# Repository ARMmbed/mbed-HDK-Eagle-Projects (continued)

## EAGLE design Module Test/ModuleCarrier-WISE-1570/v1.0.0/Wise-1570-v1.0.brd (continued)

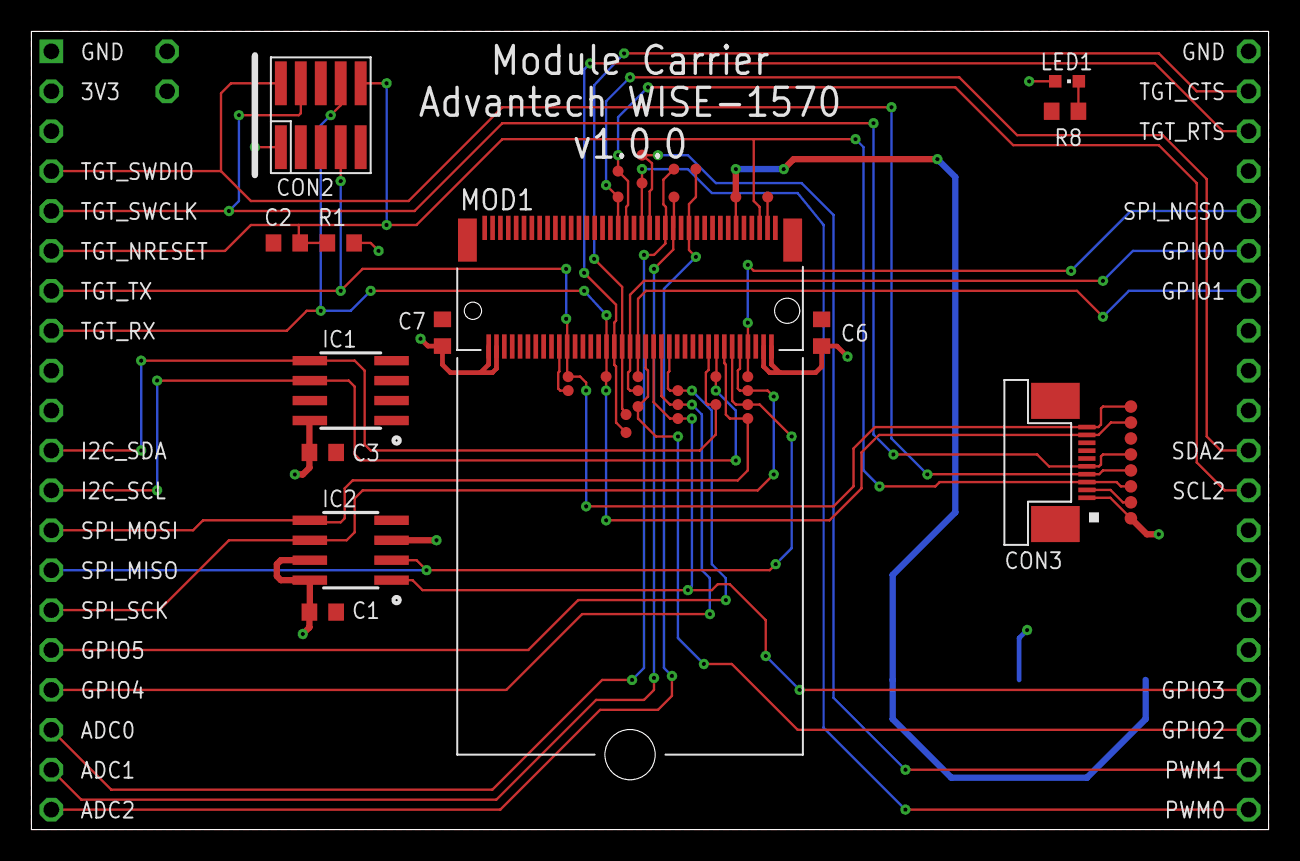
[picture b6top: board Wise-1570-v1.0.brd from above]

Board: 2 copper layers, 78.7 x 50.8 mm, 52 parts (1 on the bottom side), 33 nets.

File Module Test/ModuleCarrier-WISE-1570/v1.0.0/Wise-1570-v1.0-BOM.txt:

Partlist exported from C:/Users/cstyles/OneDrive - Arm/Documents/mbed/Projects/blackbriar/ModuleCarrier-WISE-1570/v1.0.0/Wise-1570-v1.0.sch at 15/01/2018 11:27

Qty Value              Device             Package         Parts                                                                                                                                                     Description                                                                                          
5   100nF              CAPACITOR0603      0603            C1, C2, C3, C6, C7                                                                                                                                        Capacitor                                                                                            
1   10k                RESISTOR0603       0603            R1                                                                                                                                                        Resistor                                                                                             
1   1k                 RESISTOR0603       0603            R8                                                                                                                                                        Resistor                                                                                             
1   3030               3030               3030            BAT1                                                                                                                                                      CR927, CR1025 Battery Holder for 9-10mm Cells-Tin Nickel Plated SMD                                  
1   ATECC608A          ATECC608A          SO8             IC1                                                                                                                                                                                                                                                            
1   FLOSSICORN0.25     FLOSSICORN0.25     FLOSSICORN-0.25 SS1                                                                                                                                                                                                                                                            
1   MODULE_DAUGHTER    MODULE_DAUGHTER    MODULE_DAUGHTER MOD2                                                                                                                                                                                                                                                           
1   MX25R3235FM1IH0    MX25R3235FM1IH0    SO8             IC2                                                                                                                                                       Serial Flash 32 Mb 80 Mhz                                                                            
26  PTR1TP07R          PTR1TP07R          TP07R           TP9, TP10, TP11, TP14, TP15, TP16, TP17, TP18, TP19, TP20, TP21, TP22, TP23, TP24, TP25, TP26, TP27, TP28, TP29, TP30, TP31, TP32, TP33, TP34, TP35, TP36 TEST PIN                                                                                             
8   PTR1TP08R          PTR1TP08R          TP08R           TP3, TP4, TP5, TP6, TP7, TP8, TP12, TP13                                                                                                                  TEST PIN                                                                                             
1   RED                SMD_LED0603        CHIPLED_0603    LED1                                                                                                                                                      LED SMD, Colour Red                                                                                  
1   SWD-10/TC2050_SMD  SWD-10/TC2050_SMD  FTSH-105-02     CON2                                                                                                                                                      1mm pitch 10-Pin Cortex Programming Header with optional TC2050 footprint solderless interchangeable 
1   TE-1-1734592-0     TE-1-1734592-0     TE-1-1734592-0  CON3                                                                                                                                                                                                                                                           
2   TEST-POINT-50R-PTH TEST-POINT-50R-PTH TP50-PTH        TP1, TP2                                                                                                                                                                                                                                                       
1   WISE-1570          WISE-1570          MDT420E02001    MOD1

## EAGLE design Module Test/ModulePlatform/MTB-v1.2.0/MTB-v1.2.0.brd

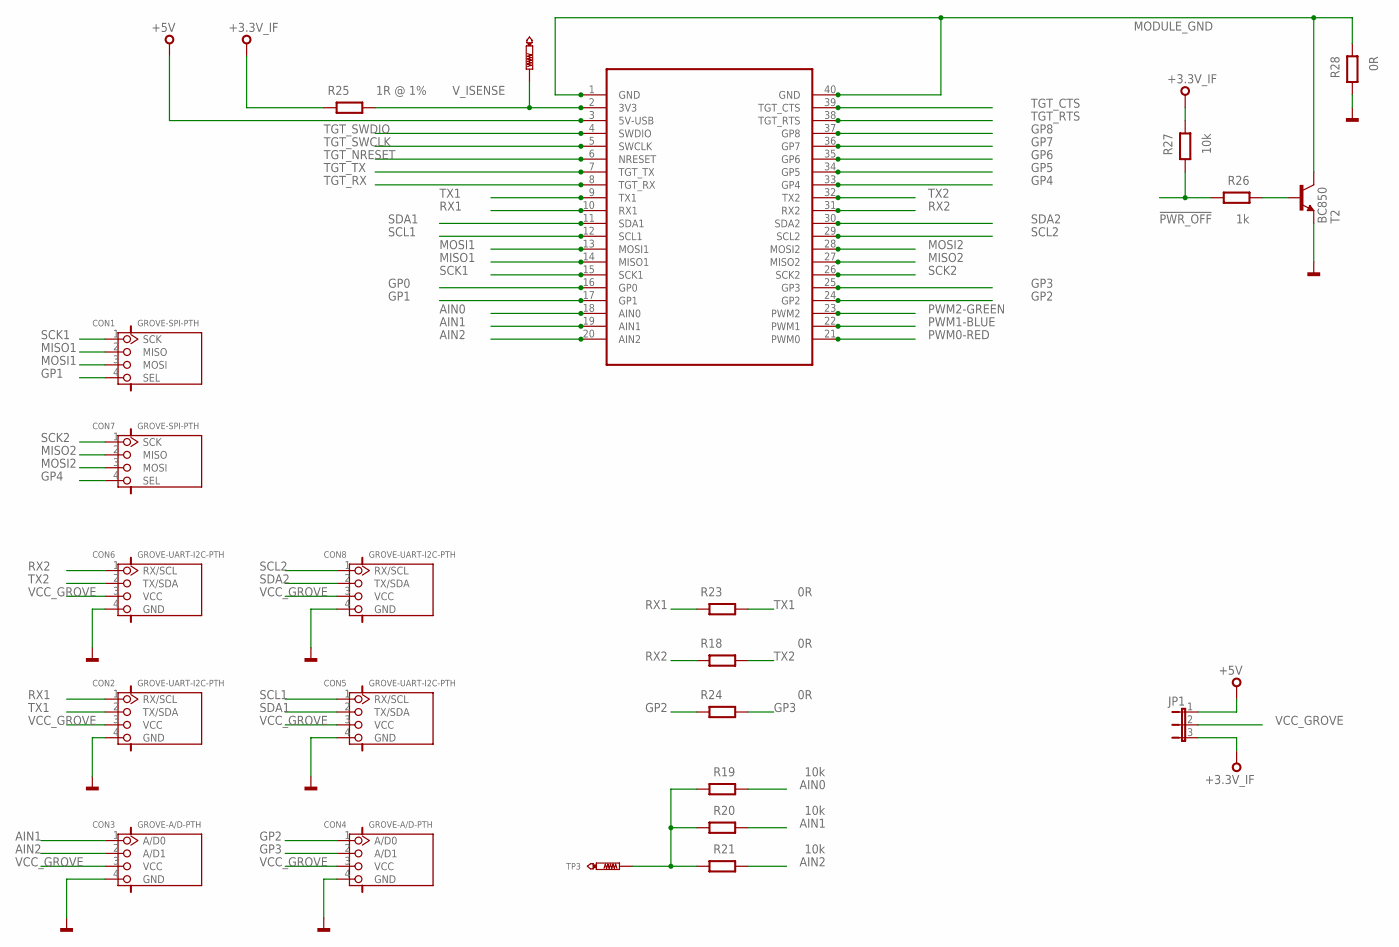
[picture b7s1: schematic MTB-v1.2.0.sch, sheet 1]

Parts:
CON1, CON7: GROVE-SPI-PTH; HW4-2.0
CON2, CON5, CON6, CON8: GROVE-UART-I2C-PTH; HW4-2.0
CON3, CON4: GROVE-A/D-PTH; HW4-2.0
JP1: JP2E; JP2
R18, R23, R24, R28: 0R; 0603@1
R19, R20, R21, R27: 10k; 0603@1
R25: 1R @ 1%; 0603@1
R26: 1k; 0603@1
SKT1: MODULE_SOCKET
T2: BC850; SOT23
TP3: TEST-POINT-50R-PTH; TP50-PTH
TP8: PTR1TP07R; TP07R

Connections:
!PWR_OFF: R26.2, R27.2; also elsewhere on the board
+3.3V_IF: JP1.3, R25.2, R27.1; also elsewhere on the board
+5V: JP1.1, SKT1.3 (5V-USB), SKT1.P$43; also elsewhere on the board
AIN0: R19.1, SKT1.18 (AIN0), SKT1.P$58; also elsewhere on the board
AIN1: CON3.1 (A/D0), R20.1, SKT1.19 (AIN1), SKT1.P$59
AIN2: CON3.2 (A/D1), R21.1, SKT1.20 (AIN2), SKT1.P$60
GND: CON2.4 (GND), CON3.4 (GND), CON4.4 (GND), CON5.4 (GND), CON6.4 (GND), CON8.4 (GND), R28.2, T2.2 (E); also elsewhere on the board
GP0: SKT1.16 (GP0), SKT1.P$56; also elsewhere on the board
GP1: CON1.4 (SEL), SKT1.17 (GP1), SKT1.P$57
GP2: CON4.1 (A/D0), R24.2, SKT1.24 (GP2), SKT1.P$64; also elsewhere on the board
GP3: CON4.2 (A/D1), R24.1, SKT1.25 (GP3), SKT1.P$65
GP4: CON7.4 (SEL), SKT1.33 (GP4), SKT1.P$73
GP5: SKT1.34 (GP5), SKT1.P$74; also elsewhere on the board
GP6: SKT1.35 (GP6), SKT1.P$75; also elsewhere on the board
GP7: SKT1.36 (GP7), SKT1.P$76; also elsewhere on the board
GP8: SKT1.37 (GP8), SKT1.P$77
MISO1: CON1.2 (MISO), SKT1.14 (MISO1), SKT1.P$54; also elsewhere on the board
MISO2: CON7.2 (MISO), SKT1.27 (MISO2), SKT1.P$67
MODULE_GND: R28.1, SKT1.1 (GND), SKT1.40 (GND), SKT1.P$41, SKT1.P$80, T2.3 (C)
MOSI1: CON1.3 (MOSI), SKT1.13 (MOSI1), SKT1.P$53; also elsewhere on the board
MOSI2: CON7.3 (MOSI), SKT1.28 (MOSI2), SKT1.P$68
unnamed: R19.2, R20.2, R21.2, TP3.TP
unnamed: R26.1, T2.1 (B)
PWM0-RED: SKT1.21 (PWM0), SKT1.P$61; also elsewhere on the board
PWM1-BLUE: SKT1.22 (PWM1), SKT1.P$62; also elsewhere on the board
PWM2-GREEN: SKT1.23 (PWM2), SKT1.P$63; also elsewhere on the board
RX1: CON2.1 (RX/SCL), R23.2, SKT1.10 (RX1), SKT1.P$50
RX2: CON6.1 (RX/SCL), R18.2, SKT1.31 (RX2), SKT1.P$71
SCK1: CON1.1 (SCK), SKT1.15 (SCK1), SKT1.P$55; also elsewhere on the board
SCK2: CON7.1 (SCK), SKT1.26 (SCK2), SKT1.P$66
SCL1: CON5.1 (RX/SCL), SKT1.12 (SCL1), SKT1.P$52; also elsewhere on the board
SCL2: CON8.1 (RX/SCL), SKT1.29 (SCL2), SKT1.P$69; also elsewhere on the board
SDA1: CON5.2 (TX/SDA), SKT1.11 (SDA1), SKT1.P$51; also elsewhere on the board
SDA2: CON8.2 (TX/SDA), SKT1.30 (SDA2), SKT1.P$70; also elsewhere on the board
TGT_CTS: SKT1.39 (TGT_CTS), SKT1.P$79; also elsewhere on the board
TGT_NRESET: SKT1.6 (NRESET), SKT1.P$46; also elsewhere on the board
TGT_RTS: SKT1.38 (TGT_RTS), SKT1.P$78; also elsewhere on the board
TGT_RX: SKT1.8 (TGT_RX), SKT1.P$48; also elsewhere on the board
TGT_SWCLK: SKT1.5 (SWCLK), SKT1.P$45; also elsewhere on the board
TGT_SWDIO: SKT1.4 (SWDIO), SKT1.P$44; also elsewhere on the board
TGT_TX: SKT1.7 (TGT_TX), SKT1.P$47; also elsewhere on the board
TX1: CON2.2 (TX/SDA), R23.1, SKT1.9 (TX1), SKT1.P$49
TX2: CON6.2 (TX/SDA), R18.1, SKT1.32 (TX2), SKT1.P$72
VCC_GROVE: CON2.3 (VCC), CON3.3 (VCC), CON4.3 (VCC), CON5.3 (VCC), CON6.3 (VCC), CON8.3 (VCC), JP1.2
V_ISENSE: R25.1, SKT1.2 (3V3), SKT1.P$42, TP8.TP; also elsewhere on the board

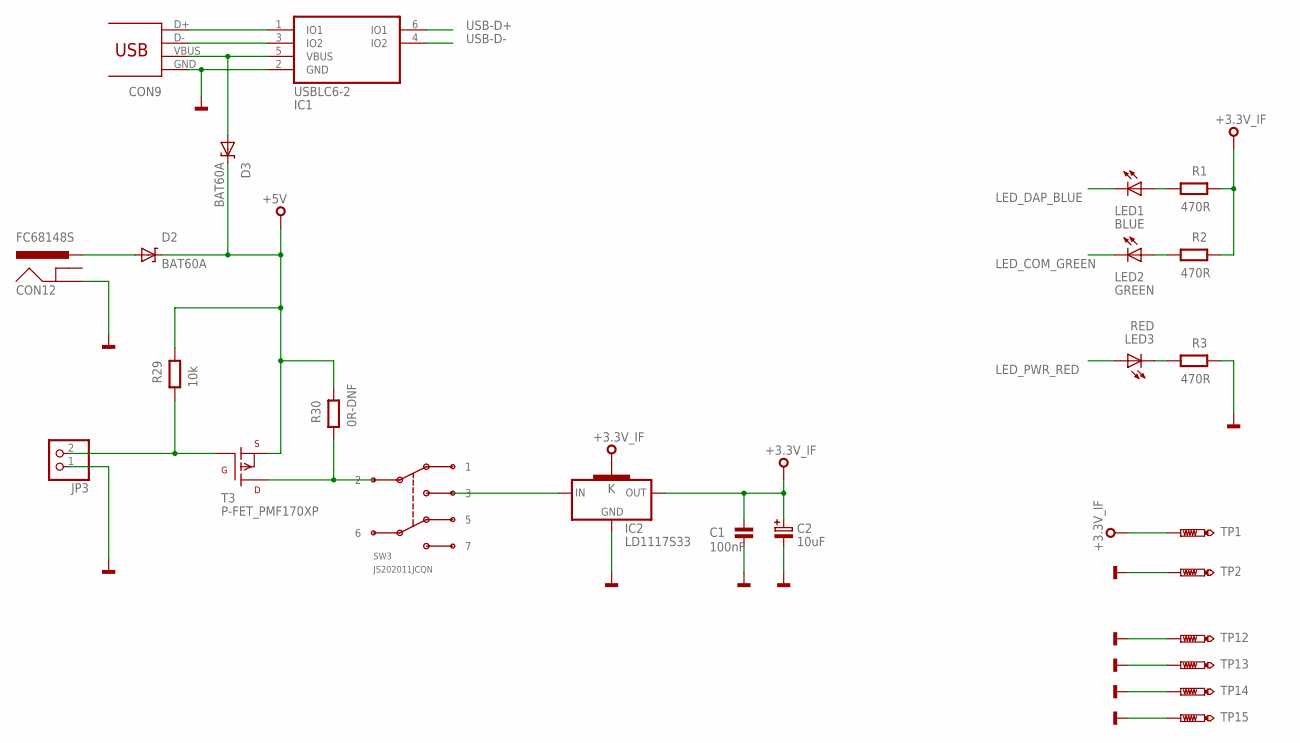
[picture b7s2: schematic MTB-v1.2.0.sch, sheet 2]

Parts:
C1: 100nF; 0603
C2: 10uF; SMC_B
CON9: USB_MICROB; MOLEX-47364-0001
CON12: FC68148S
D2, D3: BAT60A; SOD323
IC1: USBLC6-2SC6; SOT23-6L
IC2: LD1117S33; SOT223
JP3: PINHD-1X2; 1X02
LED1: BLUE; CHIPLED_0603
LED2: GREEN; CHIPLED_0603
LED3: RED; CHIPLED_0603
R1, R2, R3: 470R; 0603@1
R29: 10k; 0603@1
R30: 0R-DNF; 0603@1
SW3: JS202011JCQN
T3: P-FET_PMF170XP; SOT23-BEC
TP1, TP2, TP12, TP13, TP14, TP15: TEST-POINT-50R-PTH; TP50-PTH

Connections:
+3.3V_IF: C1.1, C2.+, IC2.2 (OUT), IC2.4 (K), R1.1, R2.1, TP1.TP; also elsewhere on the board
+5V: D2.K, D3.K, R29.1, R30.1, T3.E (S); also elsewhere on the board
GND: C1.2, C2.-, CON9.GND, CON12.3 (GND), IC1.2 (GND), IC2.1 (GND), JP3.1, R3.1, TP2.TP, TP12.TP, TP13.TP, TP14.TP, TP15.TP; also elsewhere on the board
LED_COM_GREEN: LED2.C; also elsewhere on the board
LED_DAP_BLUE: LED1.C; also elsewhere on the board
LED_PWR_RED: LED3.A; also elsewhere on the board
unnamed: CON9.D+, IC1.1 (IO1)
unnamed: CON9.D-, IC1.3 (IO2)
unnamed: LED2.A, R2.2
unnamed: LED3.C, R3.2
unnamed: LED1.A, R1.2
unnamed: CON9.VBUS, D3.A, IC1.5 (VBUS)
unnamed: R30.2, SW3.2, T3.C (D)
unnamed: CON12.1-1 (PWR), CON12.1-2 (PWR), D2.A
unnamed: IC2.3 (IN), SW3.3
unnamed: JP3.2, R29.2, T3.B (G)
USB-D+: IC1.6 (IO1); also elsewhere on the board
USB-D-: IC1.4 (IO2); also elsewhere on the board

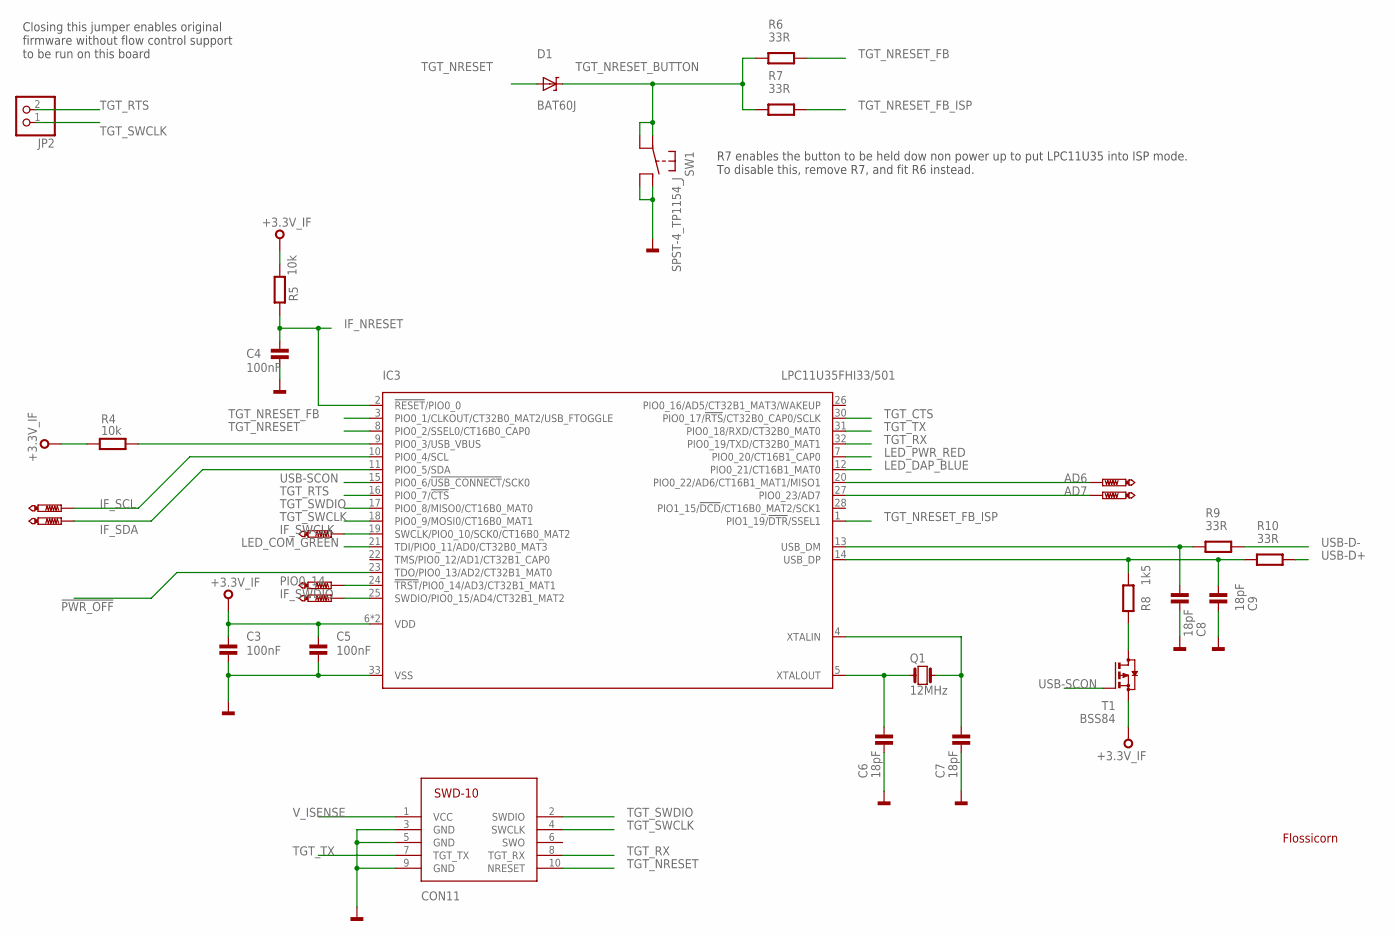
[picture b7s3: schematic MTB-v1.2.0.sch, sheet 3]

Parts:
C3, C4, C5: 100nF; 0603
C6, C7, C8, C9: 18pF; 0603
CON11: SWD-10/TC2050_SMD; FTSH-105-02
D1: BAT60J; BAT60A
IC3: LPC11U35FHI33/501; SOT617-3
JP2: PINHD-1X2; 1X02
Q1: 12MHz; 3.2X.2.5
R4, R5: 10k; 0603@1
R6, R7, R9, R10: 33R; 0603@1
R8: 1k5; 0603@1
SS1: FLOSSICORN0.5; FLOSSICORN-0.5
SW1: SPST-4_TP1154_J; TP-1154X
T1: BSS84; SOT23
TP4, TP5, TP6, TP7, TP9, TP10, TP11: PTR1TP07R; TP07R

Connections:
!PWR_OFF: IC3.23 (TDO/PIO0_13/AD2/CT32B1_MAT0); also elsewhere on the board
+3.3V_IF: C3.1, C5.1, IC3.6 (VDD), IC3.29 (VDD), R4.2, R5.2, T1.2 (S); also elsewhere on the board
AD6: IC3.20 (PIO0_22/AD6/CT16B1_MAT1/MISO1), TP7.TP
AD7: IC3.27 (PIO0_23/AD7), TP6.TP
GND: C3.2, C4.2, C5.2, C6.2, C7.2, C8.2, C9.2, CON11.3 (GND), CON11.5 (GND), CON11.9 (GND), IC3.33 (VSS), SW1.B1, SW1.B2; also elsewhere on the board
IF_NRESET: C4.1, IC3.2 (!RESET!/PIO0_0), R5.1
IF_SCL: IC3.10 (PIO0_4/SCL), TP4.TP
IF_SDA: IC3.11 (PIO0_5/SDA), TP5.TP
IF_SWCLK: IC3.19 (SWCLK/PIO0_10/SCK0/CT16B0_MAT2), TP10.TP
IF_SWDIO: IC3.25 (SWDIO/PIO0_15/AD4/CT32B1_MAT2), TP9.TP
LED_COM_GREEN: IC3.21 (TDI/PIO0_11/AD0/CT32B0_MAT3); also elsewhere on the board
LED_DAP_BLUE: IC3.12 (PIO0_21/CT16B1_MAT0); also elsewhere on the board
LED_PWR_RED: IC3.7 (PIO0_20/CT16B1_CAP0); also elsewhere on the board
unnamed: IC3.9 (PIO0_3/USB_VBUS), R4.1
unnamed: C6.1, IC3.5 (XTALOUT), Q1.P$1 (1)
unnamed: C7.1, IC3.4 (XTALIN), Q1.P$3 (2)
unnamed: R8.1, T1.3 (D)
PIO0_14: IC3.24 (!TRST!/PIO0_14/AD3/CT32B1_MAT1), TP11.TP
TGT_CTS: IC3.30 (PIO0_17/!RTS!/CT32B0_CAP0/SCLK); also elsewhere on the board
TGT_NRESET: CON11.10 (NRESET), D1.A, IC3.8 (PIO0_2/SSEL0/CT16B0_CAP0); also elsewhere on the board
TGT_NRESET_BUTTON: D1.K, R6.2, R7.2, SW1.A1, SW1.A2
TGT_NRESET_FB: IC3.3 (PIO0_1/CLKOUT/CT32B0_MAT2/USB_FTOGGLE), R6.1
TGT_NRESET_FB_ISP: IC3.1 (PIO1_19/!DTR!/SSEL1), R7.1
TGT_RTS: IC3.16 (PIO0_7/!CTS!), JP2.2; also elsewhere on the board
TGT_RX: CON11.8 (TGT_RX), IC3.32 (PIO0_19/TXD/CT32B0_MAT1); also elsewhere on the board
TGT_SWCLK: CON11.4 (SWCLK), IC3.18 (PIO0_9/MOSI0/CT16B0_MAT1), JP2.1; also elsewhere on the board
TGT_SWDIO: CON11.2 (SWDIO), IC3.17 (PIO0_8/MISO0/CT16B0_MAT0); also elsewhere on the board
TGT_TX: CON11.7 (TGT_TX), IC3.31 (PIO0_18/RXD/CT32B0_MAT0); also elsewhere on the board
USB-D+: R10.1; also elsewhere on the board
USB-D-: R9.1; also elsewhere on the board
USB-SCON: IC3.15 (PIO0_6/!USB_CONNECT!/SCK0), T1.1 (G)
USB_DM: C8.1, IC3.13 (USB_DM), R9.2
USB_DP: C9.1, IC3.14 (USB_DP), R8.2, R10.2
V_ISENSE: CON11.1 (VCC); also elsewhere on the board

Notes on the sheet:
R7 enables the button to be held dow non power up to put LPC11U35 into ISP mode. To disable this, remove R7, and fit R6 instead.
Closing this jumper enables original firmware without flow control support to be run on this board

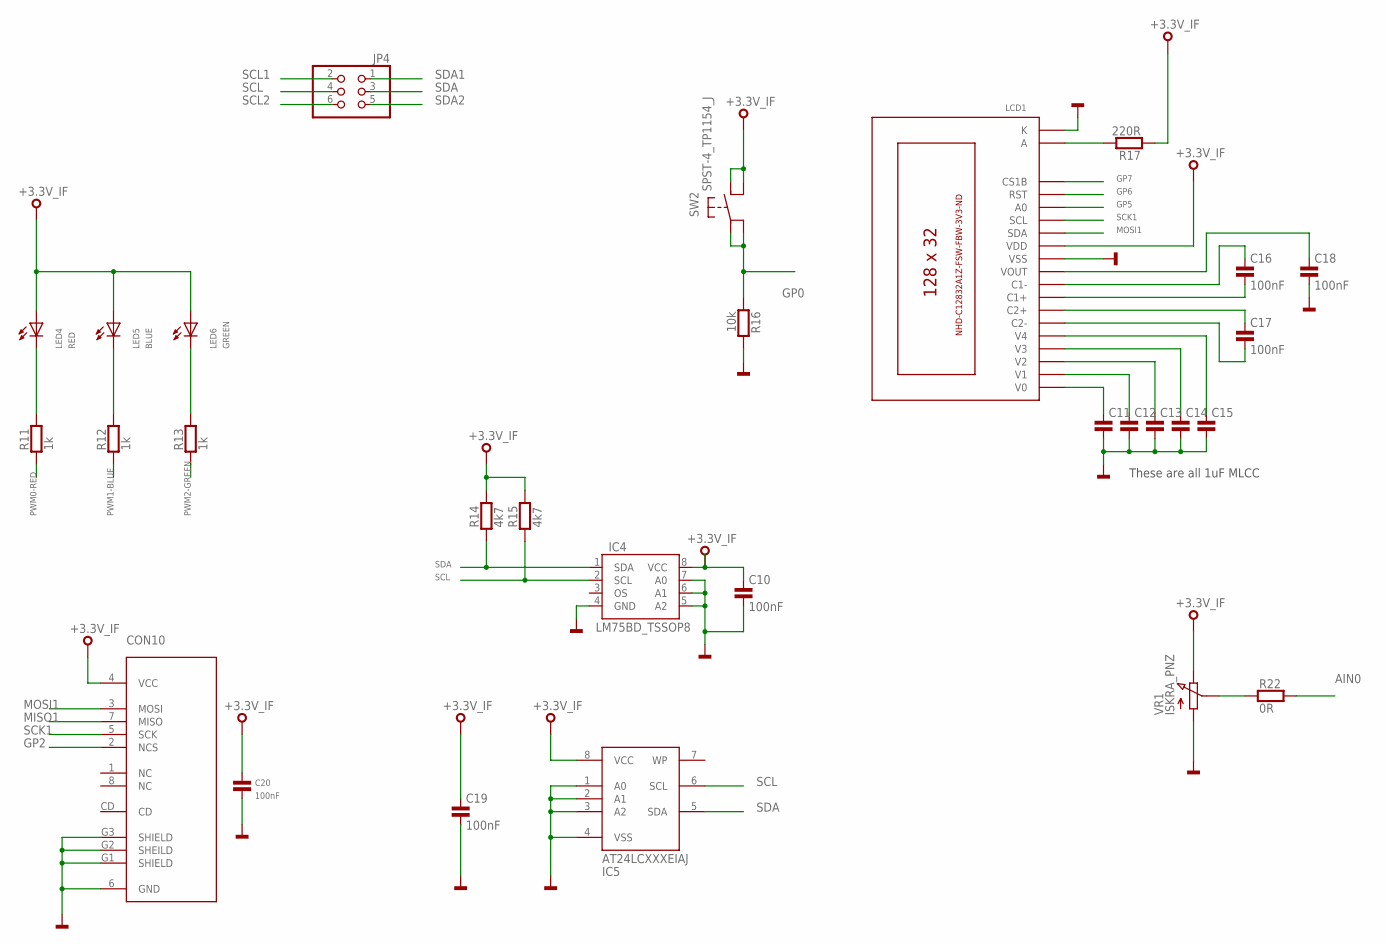
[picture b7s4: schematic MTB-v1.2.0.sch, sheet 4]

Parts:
C10, C11, C12, C13, C14, C15, C16, C17, C18, C19, C20: 100nF; 0603
CON10: MICRO-SD; AMPHENOL-101-00660-68-6
IC4: LM75BD_TSSOP8; TSSOP8
IC5: AT24LCXXXEIAJ; SO08-EIAJ
JP4: PINHD-2X3; 2X03
LCD1: C12832A1Z
LED4: RED; CHIPLED_0603
LED5: BLUE; CHIPLED_0603
LED6: GREEN; CHIPLED_0603
R11, R12, R13: 1k; 0603
R14, R15: 4k7; 0603
R16: 10k; 0603
R17: 220R; 0603
R22: 0R; 0603
SW2: SPST-4_TP1154_J; TP-1154X
VR1: ISKRA_PNZ; CA14V

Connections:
+3.3V_IF: C10.1, C19.1, C20.1, CON10.4 (VCC), IC4.8 (VCC), IC5.8 (VCC), LCD1.P$12 (VDD), LED4.A, LED5.A, LED6.A, R14.2, R15.2, R17.1, SW2.B1, SW2.B2, VR1.P$3 (E); also elsewhere on the board
AIN0: R22.2; also elsewhere on the board
GND: C10.2, C11.2, C12.2, C13.2, C14.2, C15.2, C18.2, C19.2, C20.2, CON10.6 (GND), CON10.G1 (SHIELD), CON10.G2 (SHEILD), CON10.G3 (SHIELD), IC4.4 (GND), IC4.5 (A2), IC4.6 (A1), IC4.7 (A0), IC5.1 (A0), IC5.2 (A1), IC5.3 (A2), IC5.4 (VSS), LCD1.K, LCD1.P$11 (VSS), R16.2, VR1.P$1 (A); also elsewhere on the board
GP0: R16.1, SW2.A1, SW2.A2; also elsewhere on the board
GP2: CON10.2 (NCS); also elsewhere on the board
GP5: LCD1.P$15 (A0); also elsewhere on the board
GP6: LCD1.P$16 (RST); also elsewhere on the board
GP7: LCD1.P$17 (CS1B); also elsewhere on the board
MISO1: CON10.7 (MISO); also elsewhere on the board
MOSI1: CON10.3 (MOSI), LCD1.P$13 (SDA); also elsewhere on the board
unnamed: C16.1, LCD1.P$9 (C1-)
unnamed: C17.1, LCD1.P$7 (C2+)
unnamed: C17.2, LCD1.P$6 (C2-)
unnamed: C16.2, LCD1.P$8 (C1+)
unnamed: C11.1, LCD1.P$1 (V0)
unnamed: C12.1, LCD1.P$2 (V1)
unnamed: C13.1, LCD1.P$3 (V2)
unnamed: C14.1, LCD1.P$4 (V3)
unnamed: C15.1, LCD1.P$5 (V4)
unnamed: C18.1, LCD1.P$10 (VOUT)
unnamed: LED4.C, R11.2
unnamed: LED6.C, R13.2
unnamed: LED5.C, R12.2
unnamed: LCD1.A, R17.2
unnamed: R22.1, VR1.P$2 (S)
PWM0-RED: R11.1; also elsewhere on the board
PWM1-BLUE: R12.1; also elsewhere on the board
PWM2-GREEN: R13.1; also elsewhere on the board
SCK1: CON10.5 (SCK), LCD1.P$14 (SCL); also elsewhere on the board
SCL: IC4.2 (SCL), IC5.6 (SCL), JP4.4, R15.1
SCL1: JP4.2; also elsewhere on the board
SCL2: JP4.6; also elsewhere on the board
SDA: IC4.1 (SDA), IC5.5 (SDA), JP4.3, R14.1
SDA1: JP4.1; also elsewhere on the board
SDA2: JP4.5; also elsewhere on the board

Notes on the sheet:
These are all 1uF MLCC

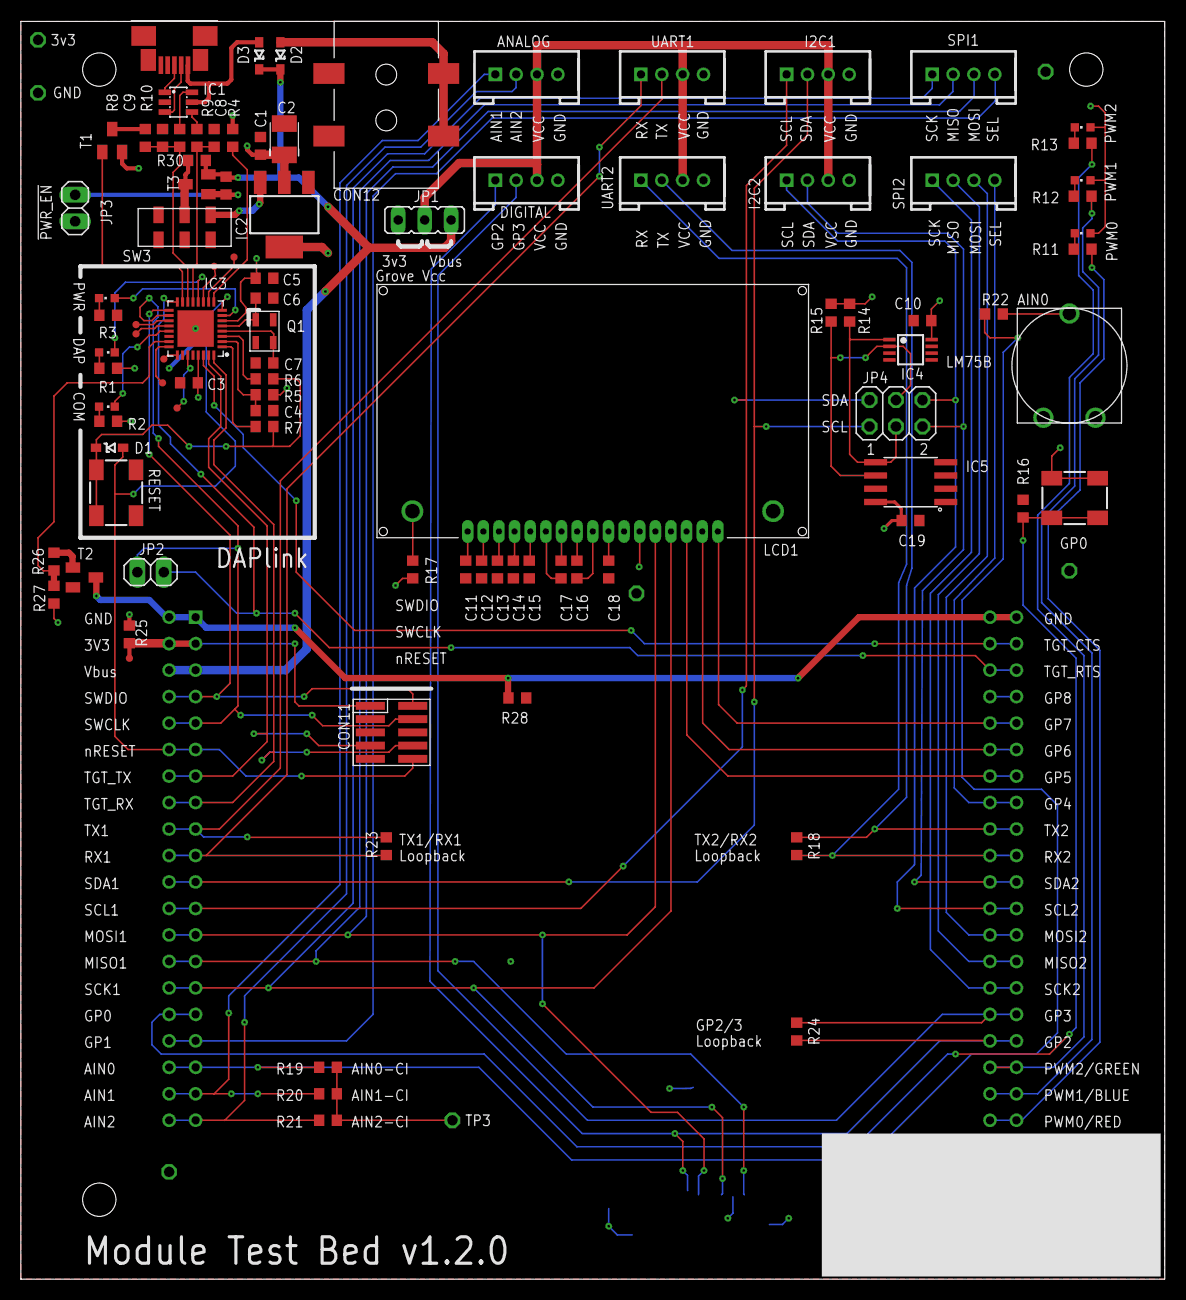
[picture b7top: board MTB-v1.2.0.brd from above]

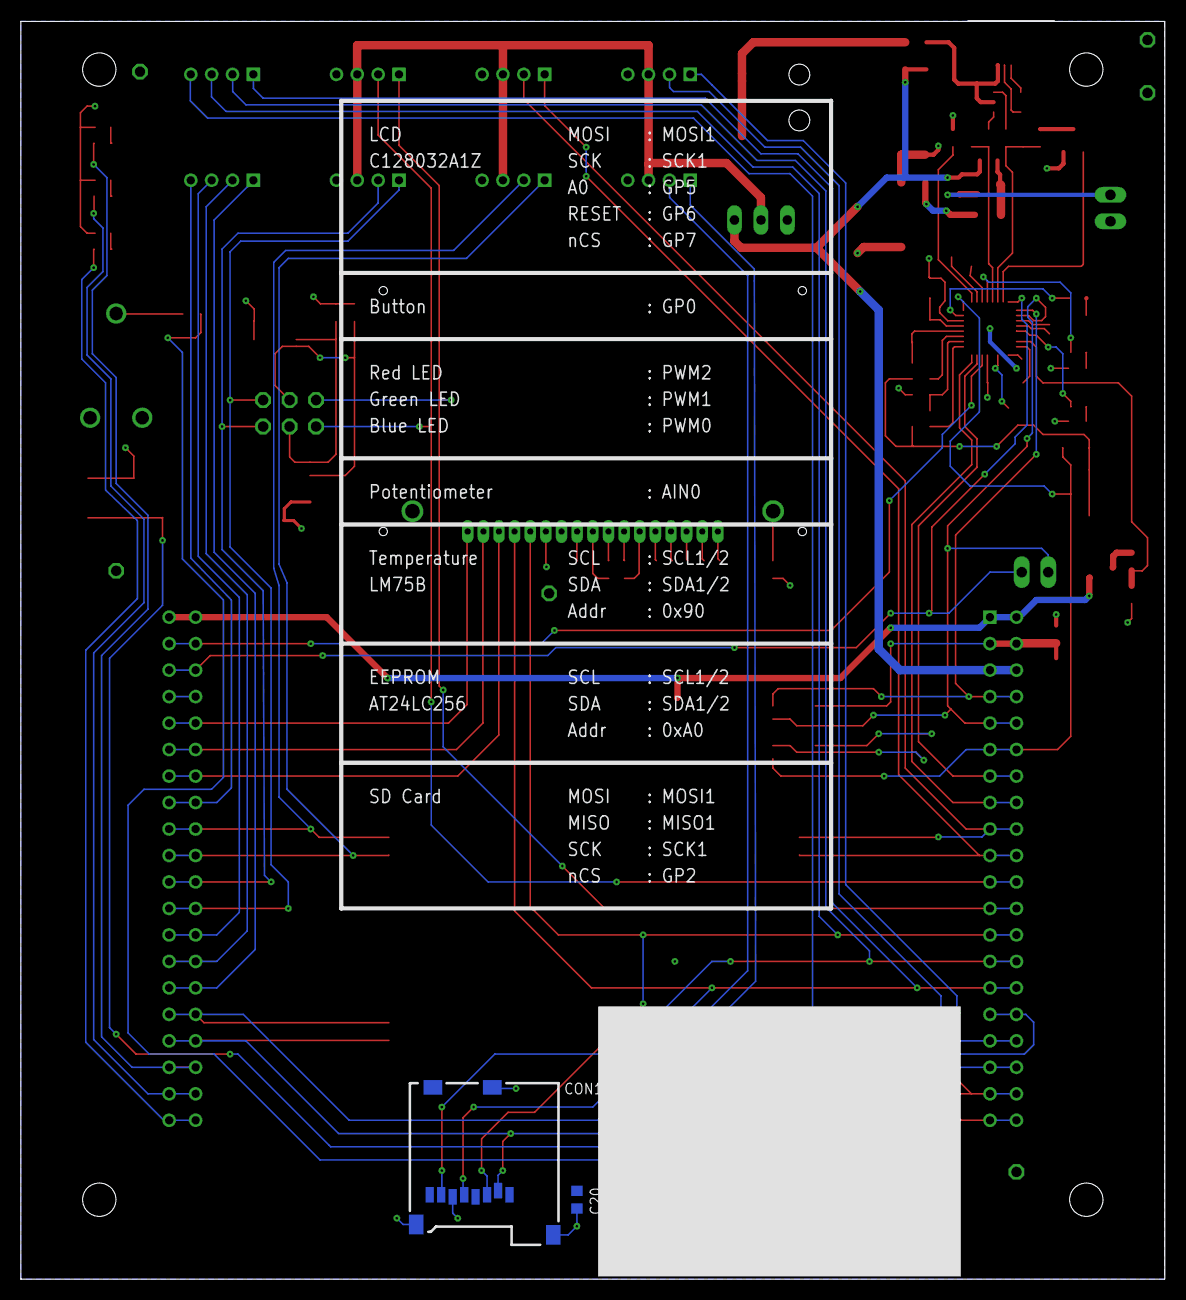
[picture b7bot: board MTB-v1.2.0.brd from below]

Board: 2 copper layers, 109.7 x 120.7 mm, 106 parts (2 on the bottom side), 95 nets.

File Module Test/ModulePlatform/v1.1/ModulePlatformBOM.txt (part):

Partlist exported from C:/Users/cstyles/Documents/mbed/Projects/blackbriar/ModulePlatform/v1.1/ModulePlatform.sch at 27/11/2017 20:35

Qty Value              Device             Package                 Parts                                                                 Description                                                                                          FLASH GPIO MF             MFN          OC-DIGIKEY    OC-MOUSER        OC-NEWARK SRAM
1                      JP2E               JP2                     JP1                                                                   JUMPER                                                                                                                                                                                   
1                      PINHD-1X2          1X02                    JP2                                                                   PIN HEADER                                                                                                                                                                               
2                      SJ2W               SJ_2                    SJ1, SJ2                                                              SMD solder JUMPER                                                                                                                                                                        
4   0R                 R0603              0603                    R22, R18, R23, R24                                                                                                                                                                                                                                             
15  100nF              C0603              0603                    C1, C3, C4, C5, C10, C11, C12, C13, C14, C15, C16, C17, C18, C19, C20 Capacitor                                                                                                                                                                                
5   10k                R0603              0603@1                  R4, R5, R19, R20, R21                                                                                                                                                                                                                                          
1   10uF               C-POLB             SMC_B                   C2                                                                    Polarised capacitor                                                                                                                                                                      
1   12MHz              Q_3.2X2.5          3.2X.2.5                Q1                                                                                                                                                                                                                                                             
4   18pF               C0603              0603                    C6, C7, C8, C9                                                        Capacitor                                                                                                                                                                                
3   1k                 R0603              0603                    R11, R12, R13                                                                                                                                                                                                                                                  
1   1k5                R0603              0603@1                  R8                                                                                                                                                                                                                                                             
2   220R               R0603              0603                    R16, R17                                                                                                                                                                                                                                                       
4   33R                R0603              0603@1                  R6, R7, R9, R10                                                                                                                                                                                                                                                
3   470R               R0603              0603@1                  R1, R2, R3                                                                                                                                                                                                                                                     
2   4k7                R0603              0603                    R14, R15                                                                                                                                                                                                                                                       
1   AT24LCXXXEIAJ      AT24LCXXXEIAJ      SO08-EIAJ               IC5                                                                   I2C EEPROM, 24LC family                                                                                                                                                                  
1   BAT60J             BAT60A             BAT60A                  D1                                                                    Schottky Diode                                                                                                                                                                           
2   BLUE               LED0603            CHIPLED_0603            LED1, LED5                                                            SMD LED                                                                                                                                                                                  
1   BSS84              BSS84              SOT23                   T1                                                                    P-CHANNEL MOS FET                                                                                                                                                                        
1   C12832A1Z          C12832A1Z          C12832A1Z               LCD1                                                                                                                                                                                                                                                           
2   GREEN              LED0603            CHIPLED_0603            LED2, LED6                                                            SMD LED                                                                                                                                                                                  
2   GROVE-A/D-PTH      GROVE-A/D-PTH      HW4-2.0                 CON3, CON4                                                                                                                                                                                                                                                     
2   GROVE-SPI-PTH      GROVE-SPI-PTH      HW4-2.0                 CON1, CON7                                                                                                                                                                                                                                                     
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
